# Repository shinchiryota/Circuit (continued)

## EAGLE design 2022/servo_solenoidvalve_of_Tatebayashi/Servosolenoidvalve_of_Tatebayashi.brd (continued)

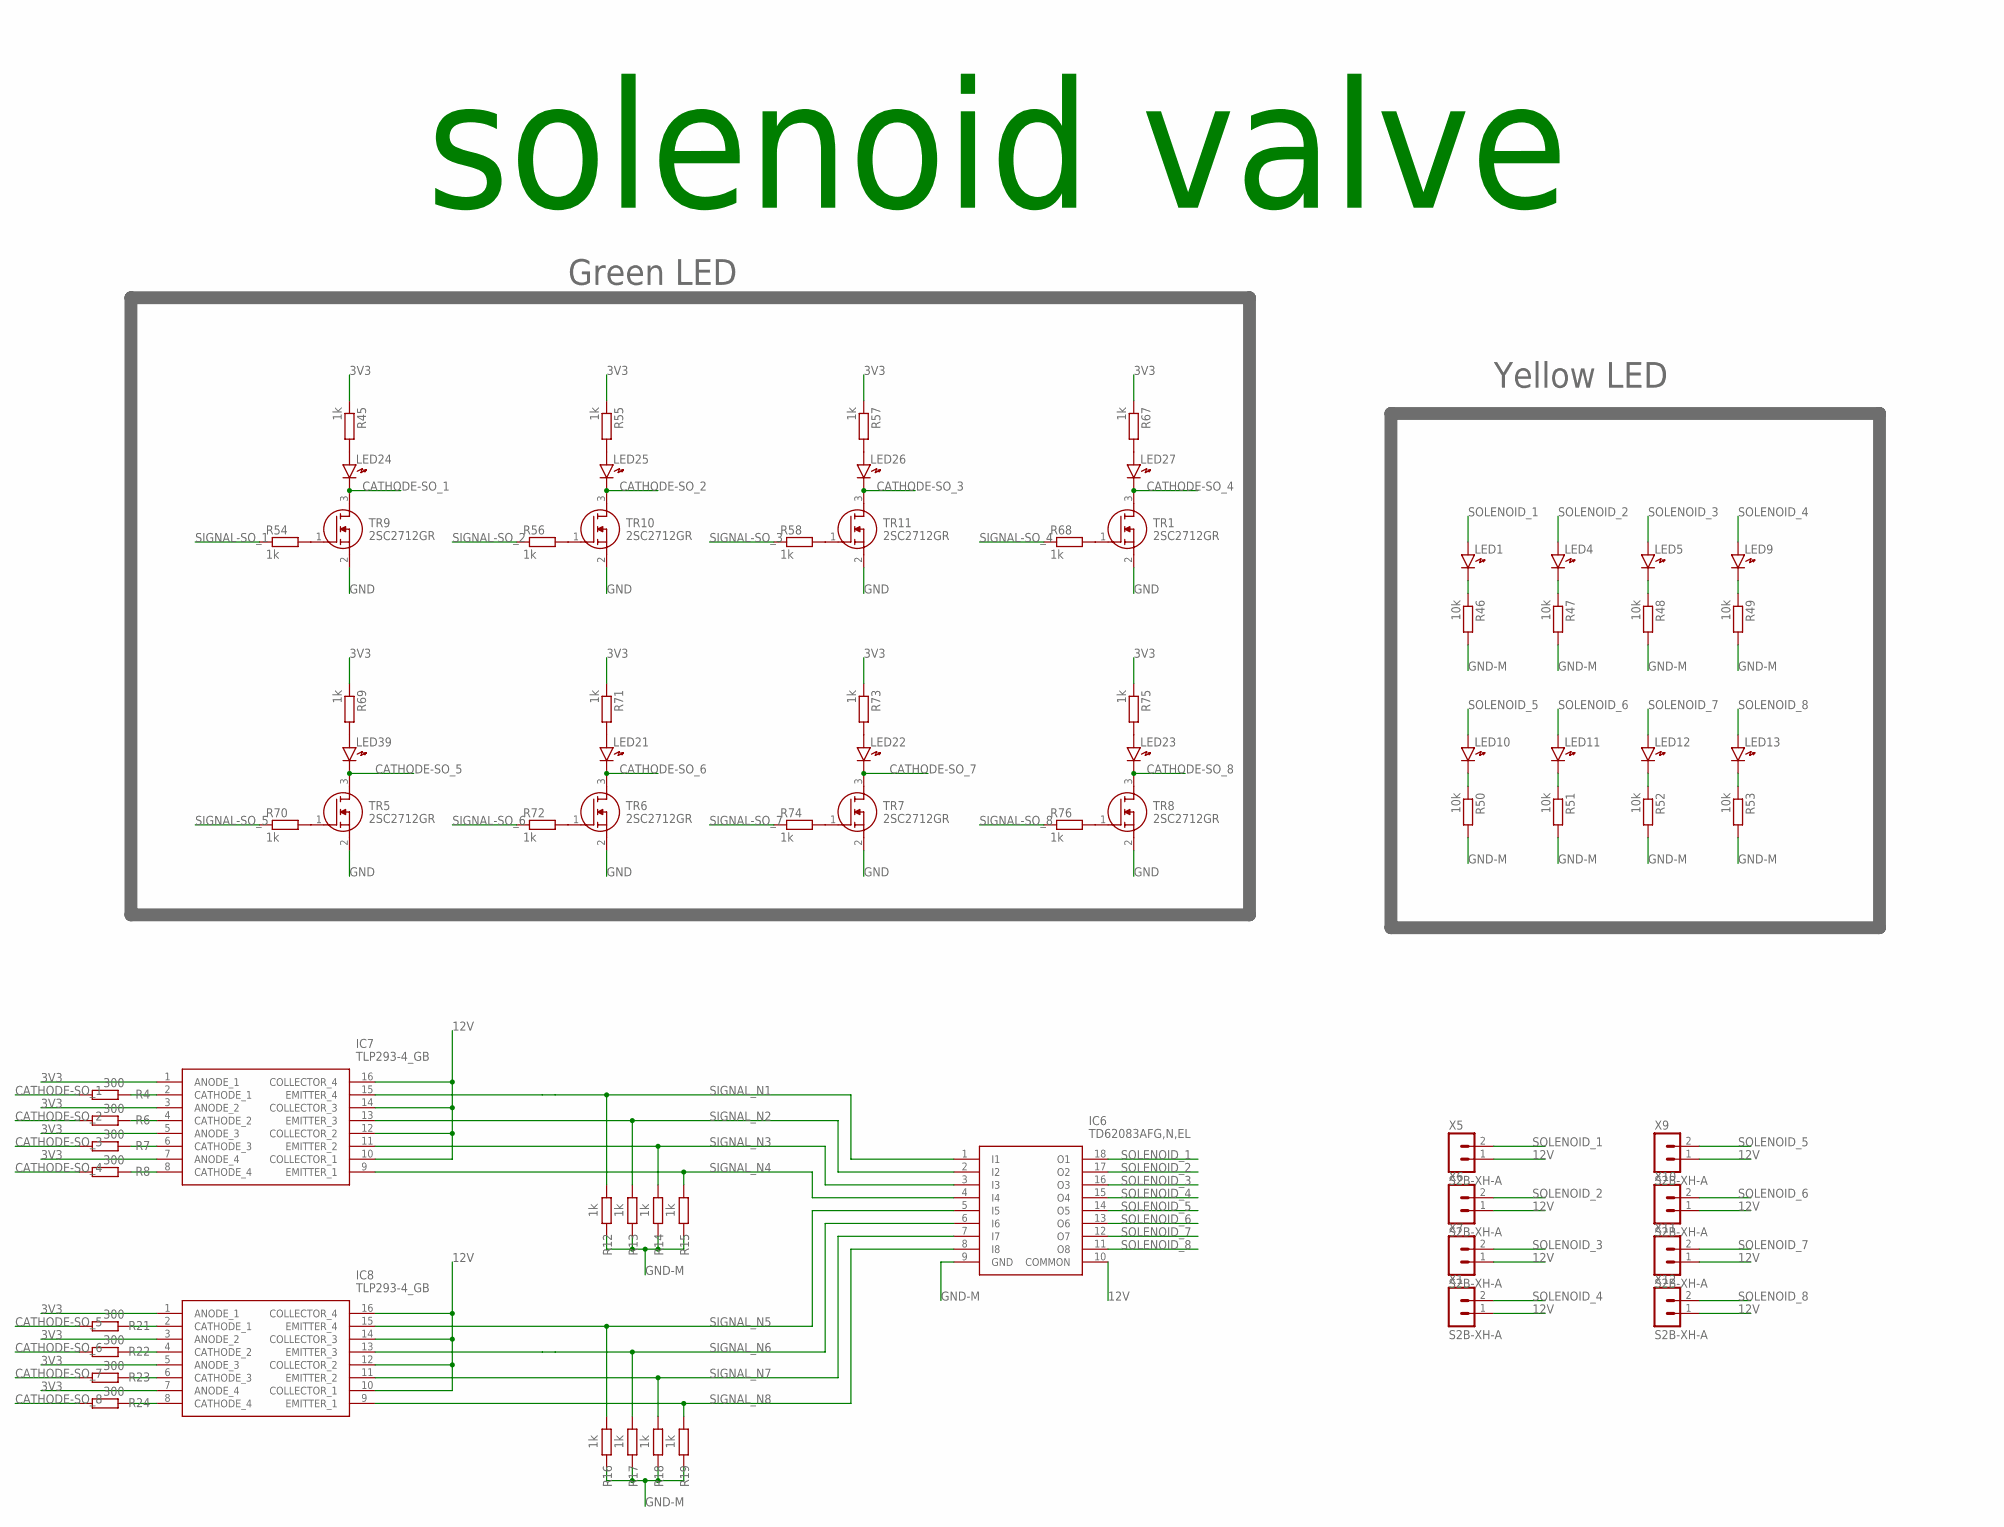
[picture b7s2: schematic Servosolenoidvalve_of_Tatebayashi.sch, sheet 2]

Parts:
IC6: TD62083AFG,N,EL; SOIC127P1030X245-18N
IC7, IC8: TLP293-4_GB; SOP128P700X220-16N
LED1, LED4, LED5, LED9, LED10, LED11, LED12, LED13, LED21, LED22, LED23, LED24, LED25, LED26, LED27, LED39: LED1608
R4, R6, R7, R8, R21, R22, R23, R24: 300; R0603
R12, R13, R14, R15, R16, R17, R18, R19, R45, R54, R55, R56, R57, R58, R67, R68, R69, R70, R71, R72, R73, R74, R75, R76: 1k; R0603
R46, R47, R48, R49, R50, R51, R52, R53: 10k; R0603
TR1, TR5, TR6, TR7, TR8, TR9, TR10, TR11: 2SC2712GR; SOT-23
X1, X5, X6, X7, X9, X10, X11, X12: S2B-XH-A

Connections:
3V3: IC7.1 (ANODE_1), IC7.3 (ANODE_2), IC7.5 (ANODE_3), IC7.7 (ANODE_4), IC8.1 (ANODE_1), IC8.3 (ANODE_2), IC8.5 (ANODE_3), IC8.7 (ANODE_4), R45.1, R55.1, R57.1, R67.1, R69.1, R71.1, R73.1, R75.1; also elsewhere on the board
12V: IC6.10 (COMMON), IC7.10 (COLLECTOR_1), IC7.12 (COLLECTOR_2), IC7.14 (COLLECTOR_3), IC7.16 (COLLECTOR_4), IC8.10 (COLLECTOR_1), IC8.12 (COLLECTOR_2), IC8.14 (COLLECTOR_3), IC8.16 (COLLECTOR_4), X1.1, X5.1, X6.1, X7.1, X9.1, X10.1, X11.1, X12.1; also elsewhere on the board
CATHODE-SO_1: LED24.K, R4.2, TR9.3 (D)
CATHODE-SO_2: LED25.K, R6.2, TR10.3 (D)
CATHODE-SO_3: LED26.K, R7.2, TR11.3 (D)
CATHODE-SO_4: LED27.K, R8.2, TR1.3 (D)
CATHODE-SO_5: LED39.K, R21.2, TR5.3 (D)
CATHODE-SO_6: LED21.K, R22.2, TR6.3 (D)
CATHODE-SO_7: LED22.K, R23.2, TR7.3 (D)
CATHODE-SO_8: LED23.K, R24.2, TR8.3 (D)
GND: TR1.2 (S), TR5.2 (S), TR6.2 (S), TR7.2 (S), TR8.2 (S), TR9.2 (S), TR10.2 (S), TR11.2 (S); also elsewhere on the board
GND-M: IC6.9 (GND), R12.1, R13.1, R14.1, R15.1, R16.1, R17.1, R18.1, R19.1, R46.2, R47.2, R48.2, R49.2, R50.2, R51.2, R52.2, R53.2; also elsewhere on the board
unnamed: IC7.2 (CATHODE_1), R4.1
unnamed: IC7.4 (CATHODE_2), R6.1
unnamed: IC7.6 (CATHODE_3), R7.1
unnamed: IC7.8 (CATHODE_4), R8.1
unnamed: LED24.A, R45.2
unnamed: LED25.A, R55.2
unnamed: LED26.A, R57.2
unnamed: LED27.A, R67.2
unnamed: IC8.2 (CATHODE_1), R21.1
unnamed: IC8.4 (CATHODE_2), R22.1
unnamed: R54.2, TR9.1 (G)
unnamed: LED39.A, R69.2
unnamed: R68.2, TR1.1 (G)
unnamed: LED21.A, R71.2
unnamed: IC8.6 (CATHODE_3), R23.1
unnamed: IC8.8 (CATHODE_4), R24.1
unnamed: LED22.A, R73.2
unnamed: LED23.A, R75.2
unnamed: R70.2, TR5.1 (G)
unnamed: R72.2, TR6.1 (G)
unnamed: R74.2, TR7.1 (G)
unnamed: R76.2, TR8.1 (G)
unnamed: R56.2, TR10.1 (G)
unnamed: R58.2, TR11.1 (G)
unnamed: LED1.K, R46.1
unnamed: LED4.K, R47.1
unnamed: LED5.K, R48.1
unnamed: LED9.K, R49.1
unnamed: LED10.K, R50.1
unnamed: LED11.K, R51.1
unnamed: LED12.K, R52.1
unnamed: LED13.K, R53.1
SIGNAL-SO_1: R54.1; also elsewhere on the board
SIGNAL-SO_2: R56.1; also elsewhere on the board
SIGNAL-SO_3: R58.1; also elsewhere on the board
SIGNAL-SO_4: R68.1; also elsewhere on the board
SIGNAL-SO_5: R70.1; also elsewhere on the board
SIGNAL-SO_6: R72.1; also elsewhere on the board
SIGNAL-SO_7: R74.1; also elsewhere on the board
SIGNAL-SO_8: R76.1; also elsewhere on the board
SIGNAL_N1: IC6.1 (I1), IC7.15 (EMITTER_4), R12.2
SIGNAL_N2: IC6.2 (I2), IC7.13 (EMITTER_3), R13.2
SIGNAL_N3: IC6.3 (I3), IC7.11 (EMITTER_2), R14.2
SIGNAL_N4: IC6.4 (I4), IC7.9 (EMITTER_1), R15.2
SIGNAL_N5: IC6.5 (I5), IC8.15 (EMITTER_4), R16.2
SIGNAL_N6: IC6.6 (I6), IC8.13 (EMITTER_3), R17.2
SIGNAL_N7: IC6.7 (I7), IC8.11 (EMITTER_2), R18.2
SIGNAL_N8: IC6.8 (I8), IC8.9 (EMITTER_1), R19.2
SOLENOID_1: IC6.18 (O1), LED1.A, X5.2
SOLENOID_2: IC6.17 (O2), LED4.A, X6.2
SOLENOID_3: IC6.16 (O3), LED5.A, X7.2
SOLENOID_4: IC6.15 (O4), LED9.A, X1.2
SOLENOID_5: IC6.14 (O5), LED10.A, X9.2
SOLENOID_6: IC6.13 (O6), LED11.A, X10.2
SOLENOID_7: IC6.12 (O7), LED12.A, X11.2
SOLENOID_8: IC6.11 (O8), LED13.A, X12.2

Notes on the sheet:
solenoid valve
Green LED
Yellow LED

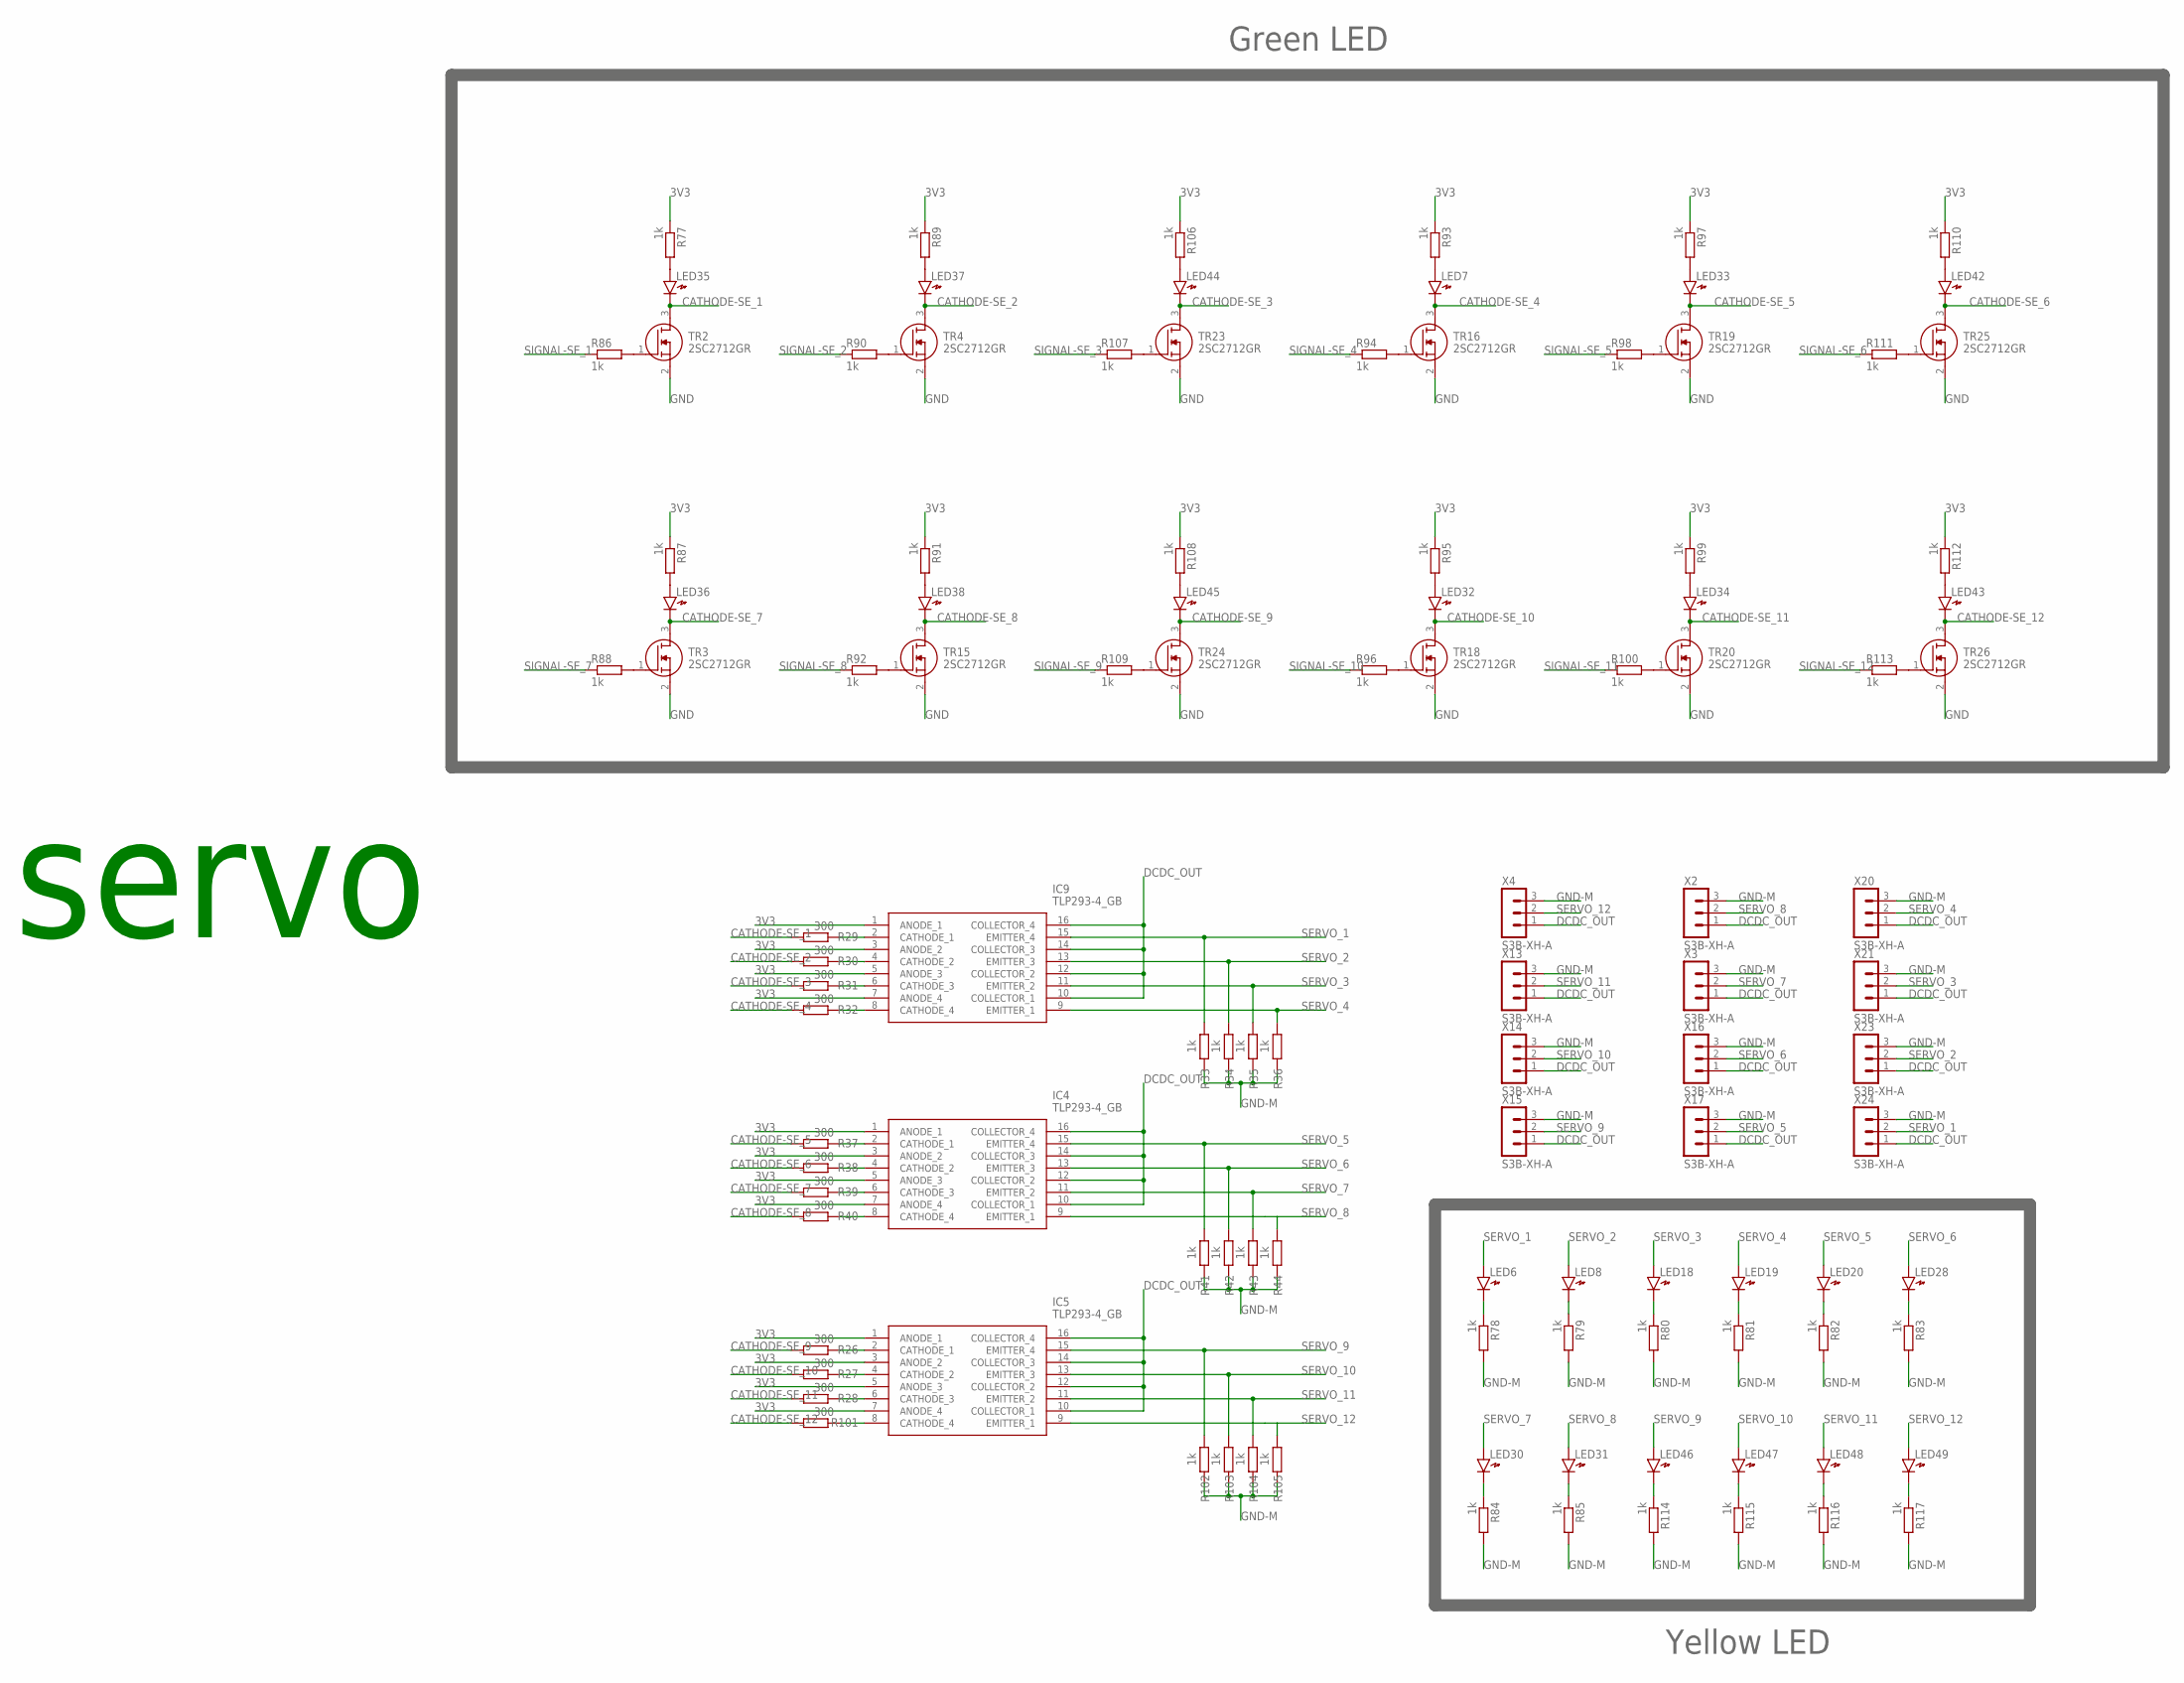
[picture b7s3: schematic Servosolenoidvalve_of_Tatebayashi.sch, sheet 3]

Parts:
IC4, IC5, IC9: TLP293-4_GB; SOP128P700X220-16N
LED6, LED7, LED8, LED18, LED19, LED20, LED28, LED30, LED31, LED32, LED33, LED34, LED35, LED36, LED37, LED38, LED42, LED43, LED44, LED45, LED46, LED47, LED48, LED49: LED1608
R26, R27, R28, R29, R30, R31, R32, R37, R38, R39, R40, R101: 300; R0603
R33, R34, R35, R36, R41, R42, R43, R44, R77, R78, R79, R80, R81, R82, R83, R84, R85, R86, R87, R88, R89, R90, R91, R92, R93, R94, R95, R96, R97, R98, R99, R100, R102, R103, R104, R105, R106, R107, R108, R109, R110, R111, R112, R113, R114, R115, R116, R117: 1k; R0603
TR2, TR3, TR4, TR15, TR16, TR18, TR19, TR20, TR23, TR24, TR25, TR26: 2SC2712GR; SOT-23
X2, X3, X4, X13, X14, X15, X16, X17, X20, X21, X23, X24: S3B-XH-A

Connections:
3V3: IC4.1 (ANODE_1), IC4.3 (ANODE_2), IC4.5 (ANODE_3), IC4.7 (ANODE_4), IC5.1 (ANODE_1), IC5.3 (ANODE_2), IC5.5 (ANODE_3), IC5.7 (ANODE_4), IC9.1 (ANODE_1), IC9.3 (ANODE_2), IC9.5 (ANODE_3), IC9.7 (ANODE_4), R77.1, R87.1, R89.1, R91.1, R93.1, R95.1, R97.1, R99.1, R106.1, R108.1, R110.1, R112.1; also elsewhere on the board
CATHODE-SE_1: LED35.K, R29.2, TR2.3 (D)
CATHODE-SE_2: LED37.K, R30.2, TR4.3 (D)
CATHODE-SE_3: LED44.K, R31.2, TR23.3 (D)
CATHODE-SE_4: LED7.K, R32.2, TR16.3 (D)
CATHODE-SE_5: LED33.K, R37.2, TR19.3 (D)
CATHODE-SE_6: LED42.K, R38.2, TR25.3 (D)
CATHODE-SE_7: LED36.K, R39.2, TR3.3 (D)
CATHODE-SE_8: LED38.K, R40.2, TR15.3 (D)
CATHODE-SE_9: LED45.K, R26.2, TR24.3 (D)
CATHODE-SE_10: LED32.K, R27.2, TR18.3 (D)
CATHODE-SE_11: LED34.K, R28.2, TR20.3 (D)
CATHODE-SE_12: LED43.K, R101.2, TR26.3 (D)
DCDC_OUT: IC4.10 (COLLECTOR_1), IC4.12 (COLLECTOR_2), IC4.14 (COLLECTOR_3), IC4.16 (COLLECTOR_4), IC5.10 (COLLECTOR_1), IC5.12 (COLLECTOR_2), IC5.14 (COLLECTOR_3), IC5.16 (COLLECTOR_4), IC9.10 (COLLECTOR_1), IC9.12 (COLLECTOR_2), IC9.14 (COLLECTOR_3), IC9.16 (COLLECTOR_4), X2.1, X3.1, X4.1, X13.1, X14.1, X15.1, X16.1, X17.1, X20.1, X21.1, X23.1, X24.1; also elsewhere on the board
GND: TR2.2 (S), TR3.2 (S), TR4.2 (S), TR15.2 (S), TR16.2 (S), TR18.2 (S), TR19.2 (S), TR20.2 (S), TR23.2 (S), TR24.2 (S), TR25.2 (S), TR26.2 (S); also elsewhere on the board
GND-M: R33.1, R34.1, R35.1, R36.1, R41.1, R42.1, R43.1, R44.1, R78.2, R79.2, R80.2, R81.2, R82.2, R83.2, R84.2, R85.2, R102.1, R103.1, R104.1, R105.1, R114.2, R115.2, R116.2, R117.2, X2.3, X3.3, X4.3, X13.3, X14.3, X15.3, X16.3, X17.3, X20.3, X21.3, X23.3, X24.3; also elsewhere on the board
unnamed: IC4.2 (CATHODE_1), R37.1
unnamed: IC4.4 (CATHODE_2), R38.1
unnamed: IC4.6 (CATHODE_3), R39.1
unnamed: IC4.8 (CATHODE_4), R40.1
unnamed: R86.2, TR2.1 (G)
unnamed: R88.2, TR3.1 (G)
unnamed: IC9.2 (CATHODE_1), R29.1
unnamed: IC9.4 (CATHODE_2), R30.1
unnamed: IC9.6 (CATHODE_3), R31.1
unnamed: IC9.8 (CATHODE_4), R32.1
unnamed: R90.2, TR4.1 (G)
unnamed: R92.2, TR15.1 (G)
unnamed: R94.2, TR16.1 (G)
unnamed: R96.2, TR18.1 (G)
unnamed: R98.2, TR19.1 (G)
unnamed: R100.2, TR20.1 (G)
unnamed: IC5.2 (CATHODE_1), R26.1
unnamed: LED6.K, R78.1
unnamed: LED8.K, R79.1
unnamed: LED18.K, R80.1
unnamed: LED19.K, R81.1
unnamed: LED20.K, R82.1
unnamed: LED28.K, R83.1
unnamed: LED30.K, R84.1
unnamed: LED31.K, R85.1
unnamed: LED35.A, R77.2
unnamed: IC5.4 (CATHODE_2), R27.1
unnamed: LED36.A, R87.2
unnamed: IC5.6 (CATHODE_3), R28.1
unnamed: LED37.A, R89.2
unnamed: IC5.8 (CATHODE_4), R101.1
unnamed: LED38.A, R91.2
unnamed: LED7.A, R93.2
unnamed: LED32.A, R95.2
unnamed: LED33.A, R97.2
unnamed: LED34.A, R99.2
unnamed: R107.2, TR23.1 (G)
unnamed: R109.2, TR24.1 (G)
unnamed: R111.2, TR25.1 (G)
unnamed: R113.2, TR26.1 (G)
unnamed: LED44.A, R106.2
unnamed: LED45.A, R108.2
unnamed: LED42.A, R110.2
unnamed: LED43.A, R112.2
unnamed: LED46.K, R114.1
unnamed: LED47.K, R115.1
unnamed: LED48.K, R116.1
unnamed: LED49.K, R117.1
SERVO_1: IC9.15 (EMITTER_4), LED6.A, R33.2, X24.2
SERVO_2: IC9.13 (EMITTER_3), LED8.A, R34.2, X23.2
SERVO_3: IC9.11 (EMITTER_2), LED18.A, R35.2, X21.2
SERVO_4: IC9.9 (EMITTER_1), LED19.A, R36.2, X20.2
SERVO_5: IC4.15 (EMITTER_4), LED20.A, R41.2, X17.2
SERVO_6: IC4.13 (EMITTER_3), LED28.A, R42.2, X16.2
SERVO_7: IC4.11 (EMITTER_2), LED30.A, R43.2, X3.2
SERVO_8: IC4.9 (EMITTER_1), LED31.A, R44.2, X2.2
SERVO_9: IC5.15 (EMITTER_4), LED46.A, R102.2, X15.2
SERVO_10: IC5.13 (EMITTER_3), LED47.A, R103.2, X14.2
SERVO_11: IC5.11 (EMITTER_2), LED48.A, R104.2, X13.2
SERVO_12: IC5.9 (EMITTER_1), LED49.A, R105.2, X4.2
SIGNAL-SE_1: R86.1; also elsewhere on the board
SIGNAL-SE_2: R90.1; also elsewhere on the board
SIGNAL-SE_3: R107.1; also elsewhere on the board
SIGNAL-SE_4: R94.1; also elsewhere on the board
SIGNAL-SE_5: R98.1; also elsewhere on the board
SIGNAL-SE_6: R111.1; also elsewhere on the board
SIGNAL-SE_7: R88.1; also elsewhere on the board
SIGNAL-SE_8: R92.1; also elsewhere on the board
SIGNAL-SE_9: R109.1; also elsewhere on the board
SIGNAL-SE_10: R96.1; also elsewhere on the board
SIGNAL-SE_11: R100.1; also elsewhere on the board
SIGNAL-SE_12: R113.1; also elsewhere on the board

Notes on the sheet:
servo
Yellow LED
Green LED

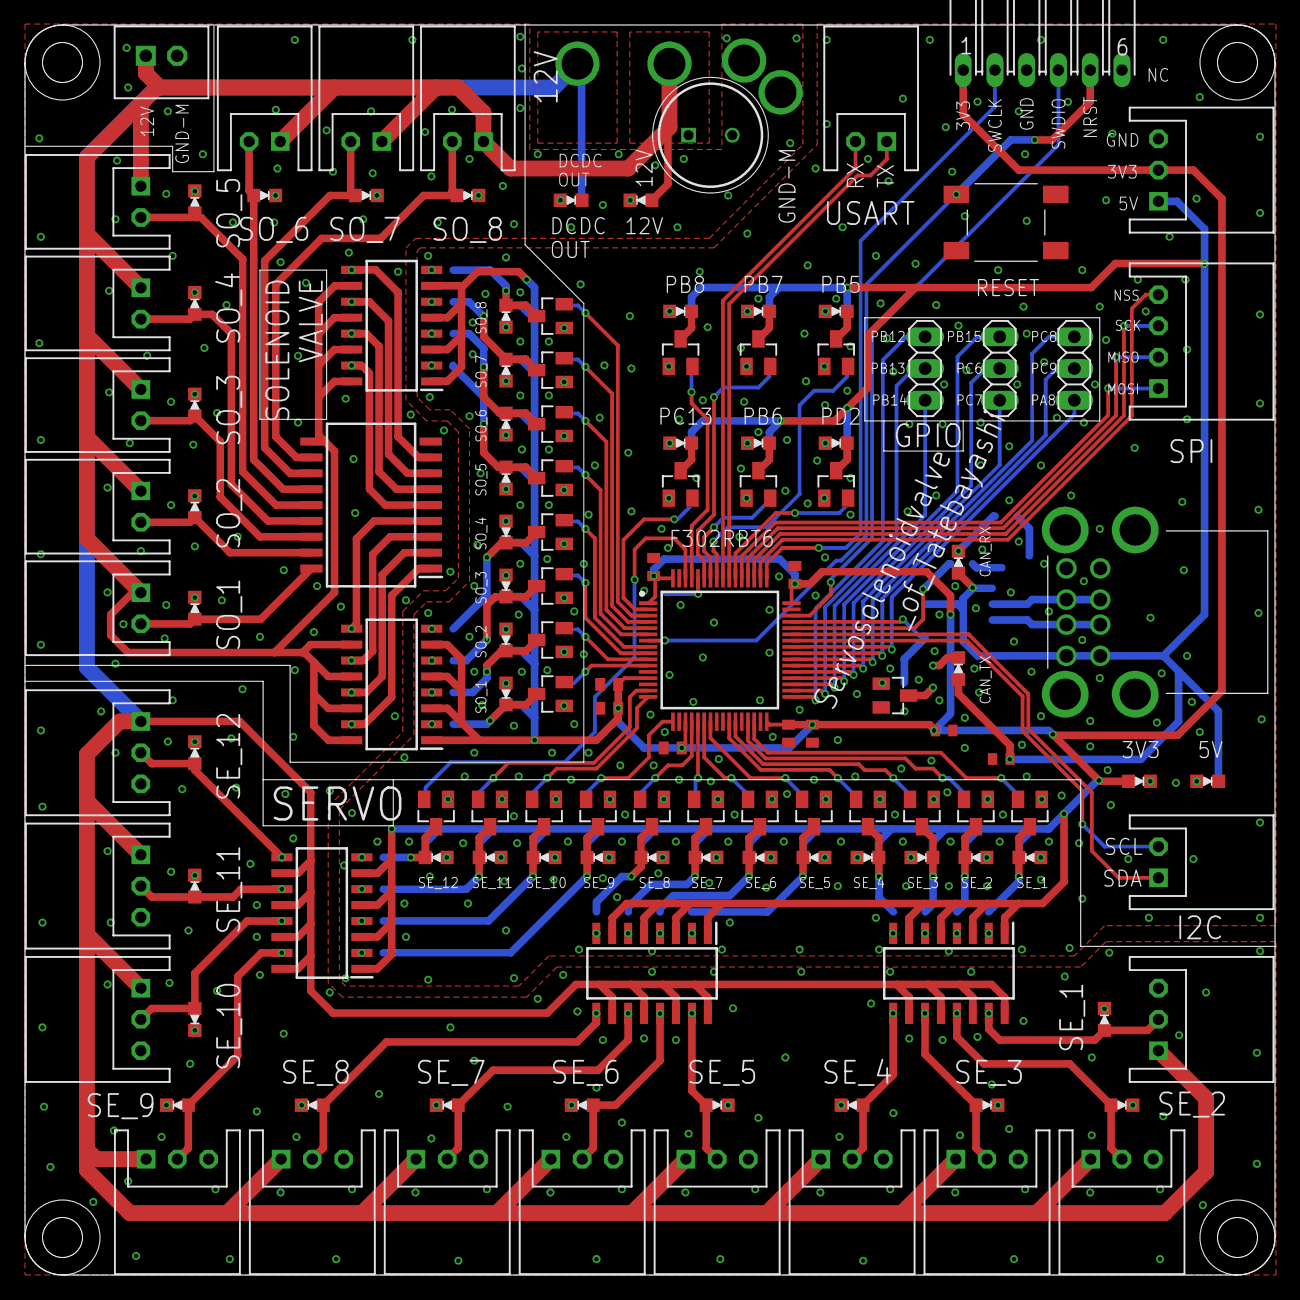
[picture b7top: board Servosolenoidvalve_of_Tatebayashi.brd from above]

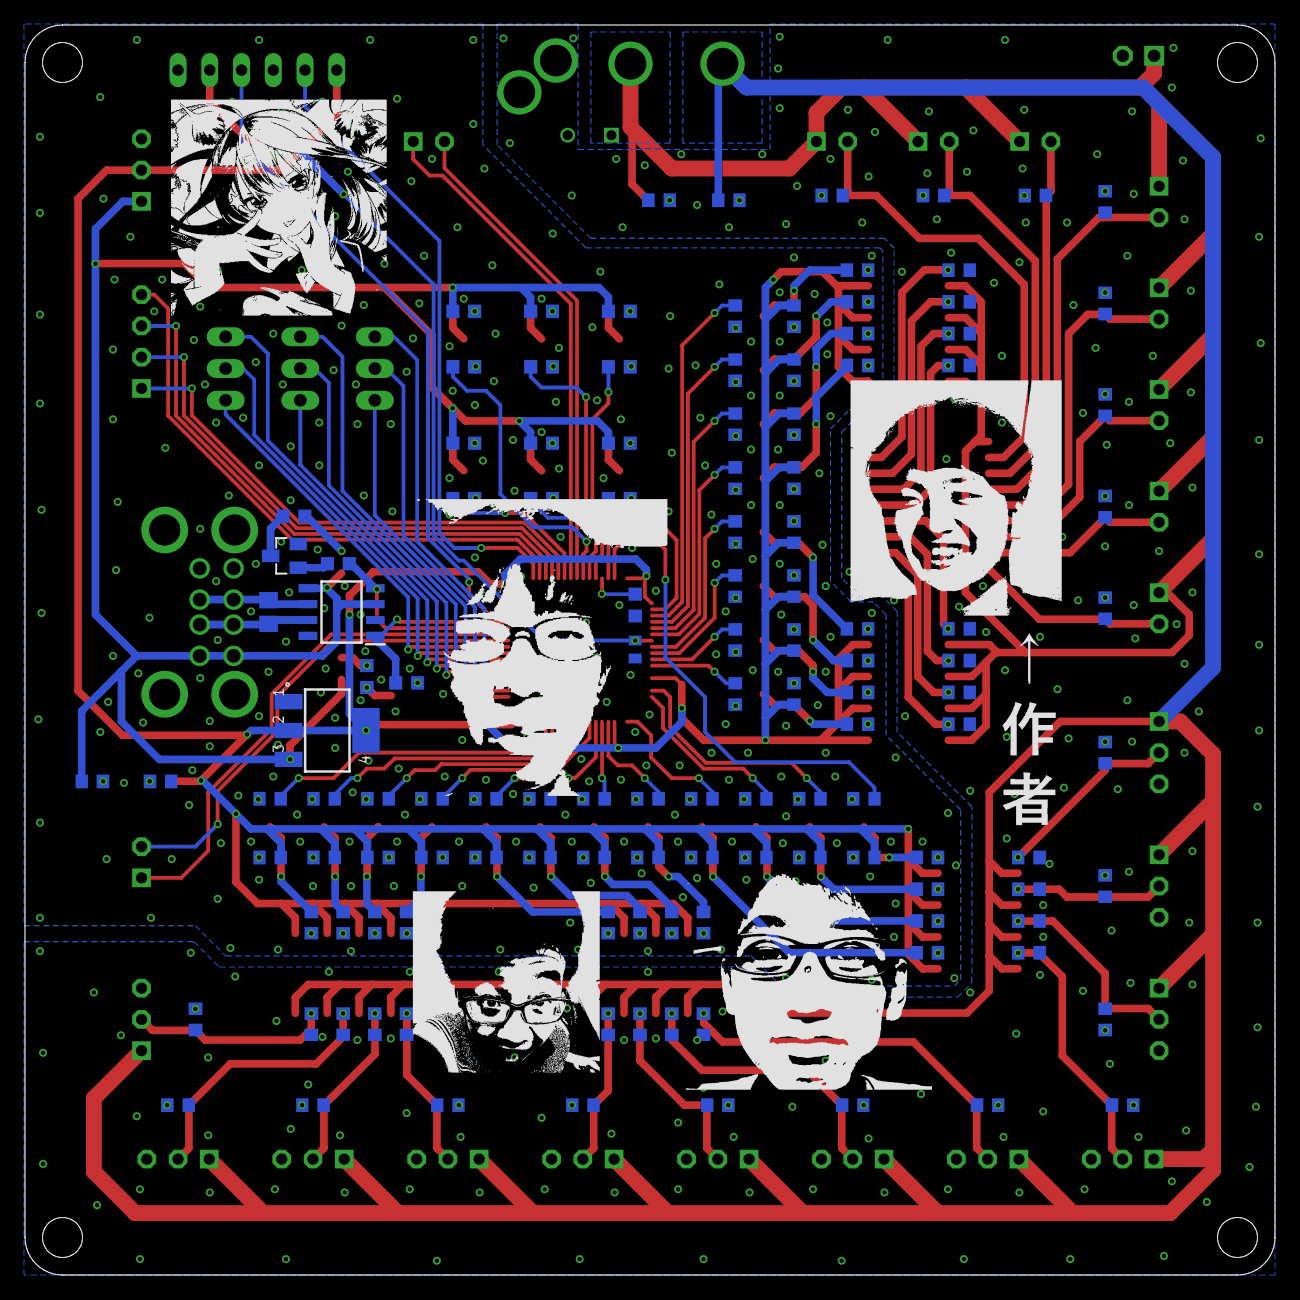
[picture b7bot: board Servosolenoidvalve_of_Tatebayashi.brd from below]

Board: 2 copper layers, 100.0 x 100.0 mm, 253 parts (126 on the bottom side), 213 nets.

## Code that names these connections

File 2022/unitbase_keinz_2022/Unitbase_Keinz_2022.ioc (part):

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Mcu.Name=STM32F732RETx
Mcu.Package=LQFP64
Mcu.UserName=STM32F732RETx
PA0-WKUP.GPIOParameters=GPIO_Label
PA0-WKUP.GPIO_Label=MD5_a
PA0-WKUP.Signal=S_TIM5_CH1
PA1.GPIOParameters=GPIO_Label
PA1.GPIO_Label=MD5_b
PA1.Signal=S_TIM5_CH2
PA11.Mode=CAN_Activate
PA11.Signal=CAN1_RX
PA12.Mode=CAN_Activate
PA12.Signal=CAN1_TX
PA13.Mode=Serial_Wire
PA13.Signal=SYS_JTMS-SWDIO
PA14.Mode=Serial_Wire
PA14.Signal=SYS_JTCK-SWCLK
PA15.Mode=NSS_Signal_Hard_Input
PA15.Signal=SPI3_NSS
PA2.GPIOParameters=GPIO_Label
PA2.GPIO_Label=MD2_a
PA2.Signal=S_TIM2_CH3
PA3.GPIOParameters=GPIO_Label
PA3.GPIO_Label=MD2_b
PA3.Signal=S_TIM2_CH4
PA5.GPIOParameters=GPIO_Label
PA5.GPIO_Label=MD1_a
PA5.Signal=S_TIM2_CH1_ETR
PA6.GPIOParameters=GPIO_Label
PA6.GPIO_Label=MD3_a
PA6.Signal=S_TIM3_CH1
PA7.GPIOParameters=GPIO_Label
PA7.GPIO_Label=MD3_b
PA7.Signal=S_TIM3_CH2
PA8.GPIOParameters=GPIO_Label
PA8.GPIO_Label=En1a
PA8.Signal=S_TIM1_CH1
PA9.GPIOParameters=GPIO_Label
PA9.GPIO_Label=En1b
PA9.Signal=S_TIM1_CH2
PB0.GPIOParameters=GPIO_Label
PB0.GPIO_Label=MD4_a
PB0.Signal=S_TIM3_CH3
PB1.GPIOParameters=GPIO_Label
PB1.GPIO_Label=MD4_b
PB1.Signal=S_TIM3_CH4
PB10.Mode=I2C
PB10.Signal=I2C2_SCL
PB11.Mode=I2C
PB11.Signal=I2C2_SDA
PB12.Signal=GPIO_Output
PB13.Signal=GPIO_Output
PB14.Signal=GPIO_Output
PB3.GPIOParameters=GPIO_Label
PB3.GPIO_Label=MD1_b
PB3.Signal=S_TIM2_CH2
PB6.Mode=Asynchronous
PB6.Signal=USART1_TX
PB7.Mode=Asynchronous
PB7.Signal=USART1_RX
PC1.Signal=GPIO_Output
PC10.Mode=Full_Duplex_Master
PC10.Signal=SPI3_SCK
PC11.Mode=Full_Duplex_Master
PC11.Signal=SPI3_MISO
PC12.Mode=Full_Duplex_Master
PC12.Signal=SPI3_MOSI
PC14-OSC32_IN.Signal=GPIO_Output
PC15-OSC32_OUT.Signal=GPIO_Input
PC2.Signal=GPIO_Output
PC3.Signal=GPIO_Output
PC6.GPIOParameters=GPIO_Label
PC6.GPIO_Label=En2a
PC6.Signal=S_TIM8_CH1
PC7.GPIOParameters=GPIO_Label
PC7.GPIO_Label=En2b
PC7.Signal=S_TIM8_CH2
PH0-OSC_IN.Signal=GPIO_Output
PH1-OSC_OUT.Signal=GPIO_Output
RCC.HSE_VALUE=25000000
board=custom

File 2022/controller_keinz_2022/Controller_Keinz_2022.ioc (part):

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Mcu.Name=STM32F302C(6-8)Tx
Mcu.Package=LQFP48
Mcu.UserName=STM32F302C8Tx
PA0.Signal=GPIO_Output
PA1.Signal=GPIO_Output
PA10.Mode=Asynchronous
PA10.Signal=USART1_RX
PA11.Mode=CTS_RTS
PA11.Signal=USART1_CTS
PA12.Mode=CTS_RTS
PA12.Signal=USART1_RTS
PA13.Mode=Serial_Wire
PA13.Signal=SYS_JTMS-SWDIO
PA14.Mode=Serial_Wire
PA14.Signal=SYS_JTCK-SWCLK
PA15.Mode=NSS_Signal_Hard_Input
PA15.Signal=SPI3_NSS
PA2.Signal=GPIO_Output
PA3.Signal=GPIO_Output
PA5.Signal=GPIO_Output
PA6.Signal=GPIO_Output
PA7.Signal=GPIO_Output
PA9.Mode=Asynchronous
PA9.Signal=USART1_TX
PB0.Signal=GPIO_Output
PB1.Signal=GPIO_Output
PB10.Signal=GPIO_Output
PB11.Signal=GPIO_Output
PB12.Signal=GPIO_Output
PB13.Signal=GPIO_Output
PB14.Signal=GPIO_Output
PB15.Signal=GPIO_Output
PB2.Signal=GPIO_Output
PB3.Mode=Full_Duplex_Master
PB3.Signal=SPI3_SCK
PB4.Mode=Full_Duplex_Master
PB4.Signal=SPI3_MISO
PB5.Mode=Full_Duplex_Master
PB5.Signal=SPI3_MOSI
PB6.Mode=I2C
PB6.Signal=I2C1_SCL
PB7.Mode=I2C
PB7.Signal=I2C1_SDA
PC13.Signal=GPIO_Output
PF0-OSC_IN.Mode=I2C
PF0-OSC_IN.Signal=I2C2_SDA
PF1-OSC_OUT.Mode=I2C
PF1-OSC_OUT.Signal=I2C2_SCL
RCC.HSEPLLFreq_Value=8000000
RCC.HSE_VALUE=8000000
RCC.SYSCLKFreq_VALUE=8000000
board=custom

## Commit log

2024-04-13 高専ロボコン2024のときに作成された回路を示すフォルダーを作成した
2024-04-13 zipファイルを解凍,ファイルの整備性を良くした
